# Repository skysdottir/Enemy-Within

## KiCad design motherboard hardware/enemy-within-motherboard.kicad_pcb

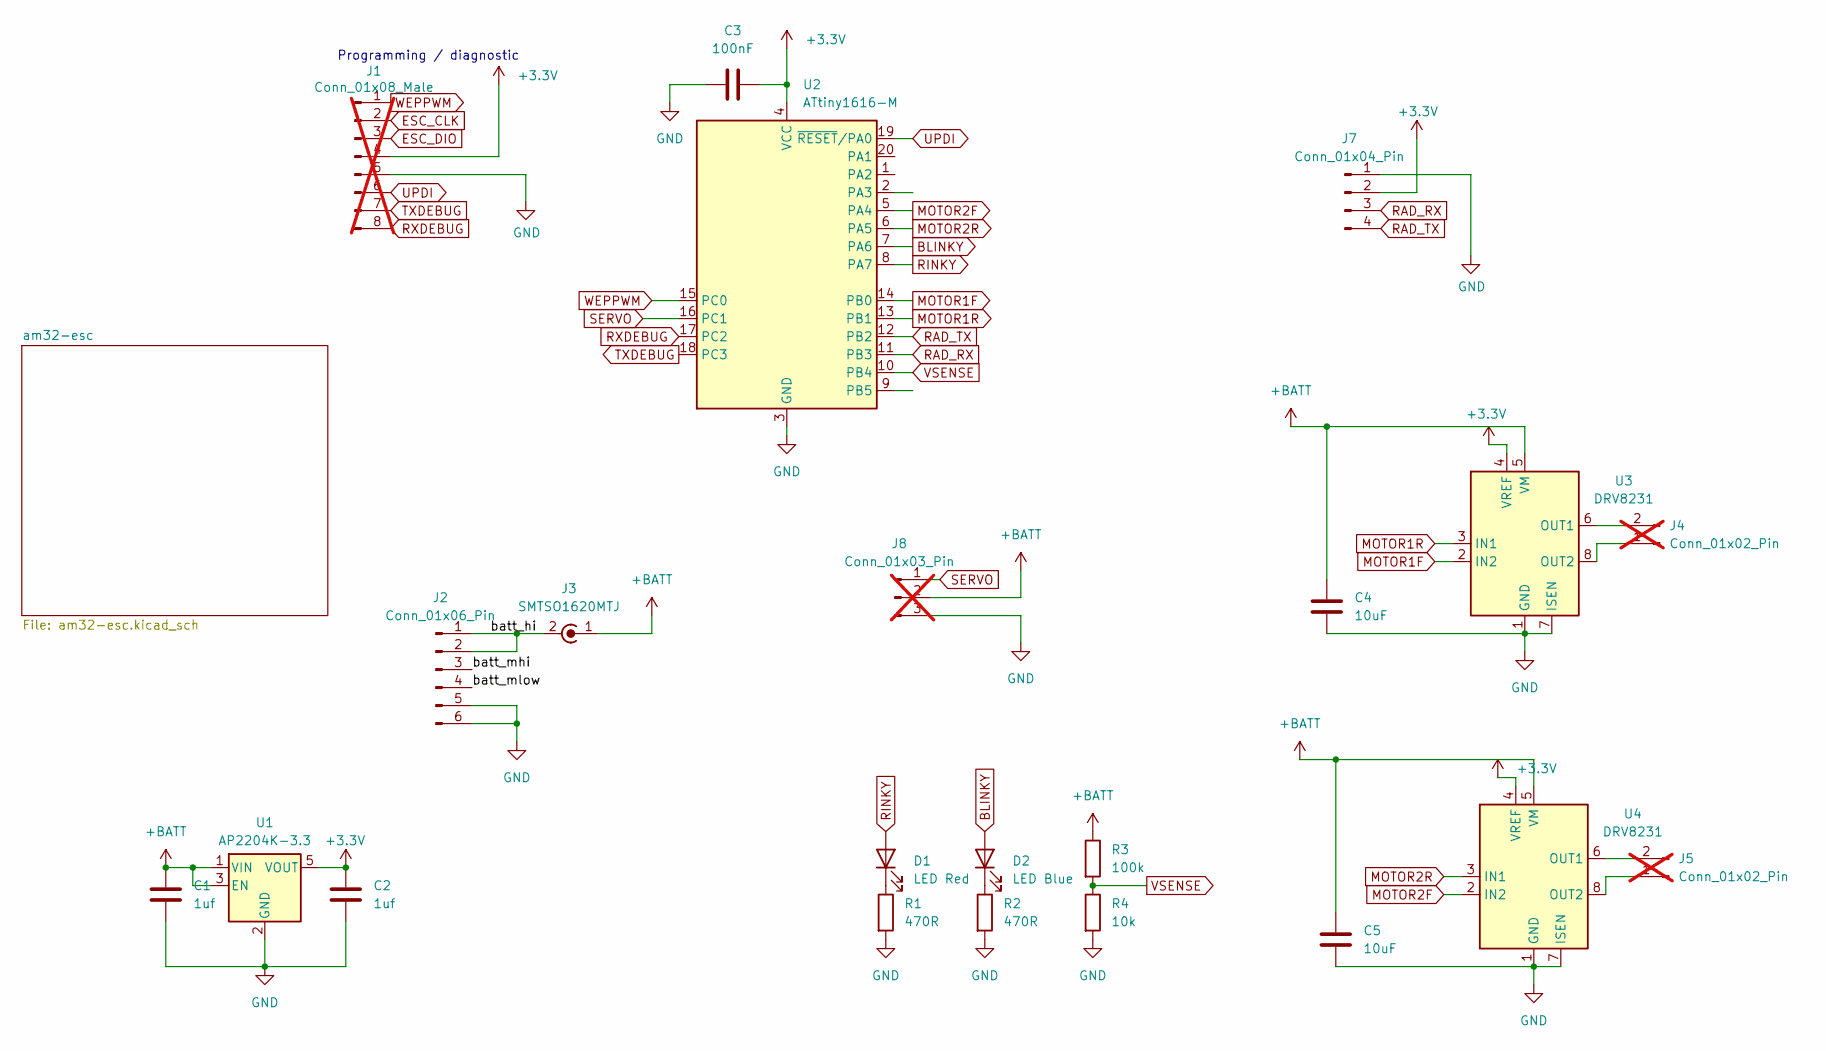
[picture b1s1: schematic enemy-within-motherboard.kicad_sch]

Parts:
C1, C2: 1uf; C_0402_1005Metric_Pad0.74x0.62mm_HandSolder
C3: 100nF; C_0402_1005Metric_Pad0.74x0.62mm_HandSolder
C4, C5: 10uF; C_0402_1005Metric_Pad0.74x0.62mm_HandSolder
D1: LED Red; LED_0603_1608Metric
D2: LED Blue; LED_0603_1608Metric
J1: Conn_01x08_Male; SOIC_clipProgSmall; not fitted
J2: Conn_01x06_Pin; JST_XH_B6B-XH-A_1x06_P2.50mm_Vertical
J3: SMTSO1620MTJ; MountingHole_2.2mm_M2_Pad_TopBottom
J4, J5: Conn_01x02_Pin; PinHeader_1x02_P2.54mm_Vertical; not fitted
J7: Conn_01x04_Pin; PinHeader_1x04_P2.54mm_Vertical
J8: Conn_01x03_Pin; PinHeader_1x03_P2.54mm_Vertical; not fitted
R1, R2: 470R; R_0402_1005Metric_Pad0.72x0.64mm_HandSolder
R3: 100k; R_0402_1005Metric_Pad0.72x0.64mm_HandSolder
R4: 10k; R_0402_1005Metric_Pad0.72x0.64mm_HandSolder
U1: AP2204K-3.3; TSOT-23-5
U2: ATtiny1616-M; VQFN-20-1EP_3x3mm_P0.4mm_EP1.7x1.7mm
U3, U4: DRV8231; WSON-8-1EP_2x2mm_P0.5mm_EP0.9x1.6mm

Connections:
+3.3V: C2.1, C3.2, J1.4, J7.2, U1.5 (VOUT), U2.4 (VCC), U3.4 (VREF), U4.4 (VREF); also elsewhere on the board
+BATT: C1.1, C4.1, C5.1, J3.1 (In), J8.2, R3.1, U1.1 (VIN), U1.3 (EN), U3.5 (VM), U4.5 (VM); also elsewhere on the board
/batt_hi: J2.1, J2.2, J3.2 (Ext)
/batt_mhi: J2.3
/batt_mlow: J2.4
BLINKY: D2.2 (A), U2.7 (PA6)
ESC_CLK: J1.2; also elsewhere on the board
ESC_DIO: J1.3; also elsewhere on the board
GND: C1.2, C2.2, C3.1, C4.2, C5.2, J1.5, J2.5, J2.6, J7.1, J8.3, R1.2, R2.2, R4.2, U1.2 (GND), U2.3 (GND), U2.21 (GND), U3.1 (GND), U3.7 (ISEN), U3.9 (GND), U4.1 (GND), U4.7 (ISEN), U4.9 (GND); also elsewhere on the board
MOTOR1F: U2.14 (PB0), U3.2 (IN2)
MOTOR1R: U2.13 (PB1), U3.3 (IN1)
MOTOR2F: U2.5 (PA4), U4.2 (IN2)
MOTOR2R: U2.6 (PA5), U4.3 (IN1)
unnamed: D1.1 (K), R1.1
unnamed: D2.1 (K), R2.1
unnamed: J4.1, U3.8 (OUT2)
unnamed: J4.2, U3.6 (OUT1)
unnamed: J5.1, U4.8 (OUT2)
unnamed: J5.2, U4.6 (OUT1)
RAD_RX: J7.3, U2.11 (PB3)
RAD_TX: J7.4, U2.12 (PB2)
RINKY: D1.2 (A), U2.8 (PA7)
RXDEBUG: J1.8, U2.17 (PC2)
SERVO: J8.1, U2.16 (PC1)
TXDEBUG: J1.7, U2.18 (PC3)
UPDI: J1.6, U2.19 (~RESET/PA0)
VSENSE: R3.2, R4.1, U2.10 (PB4); also elsewhere on the board
WEPPWM: J1.1, U2.15 (PC0); also elsewhere on the board

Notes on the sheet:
Programming / diagnostic

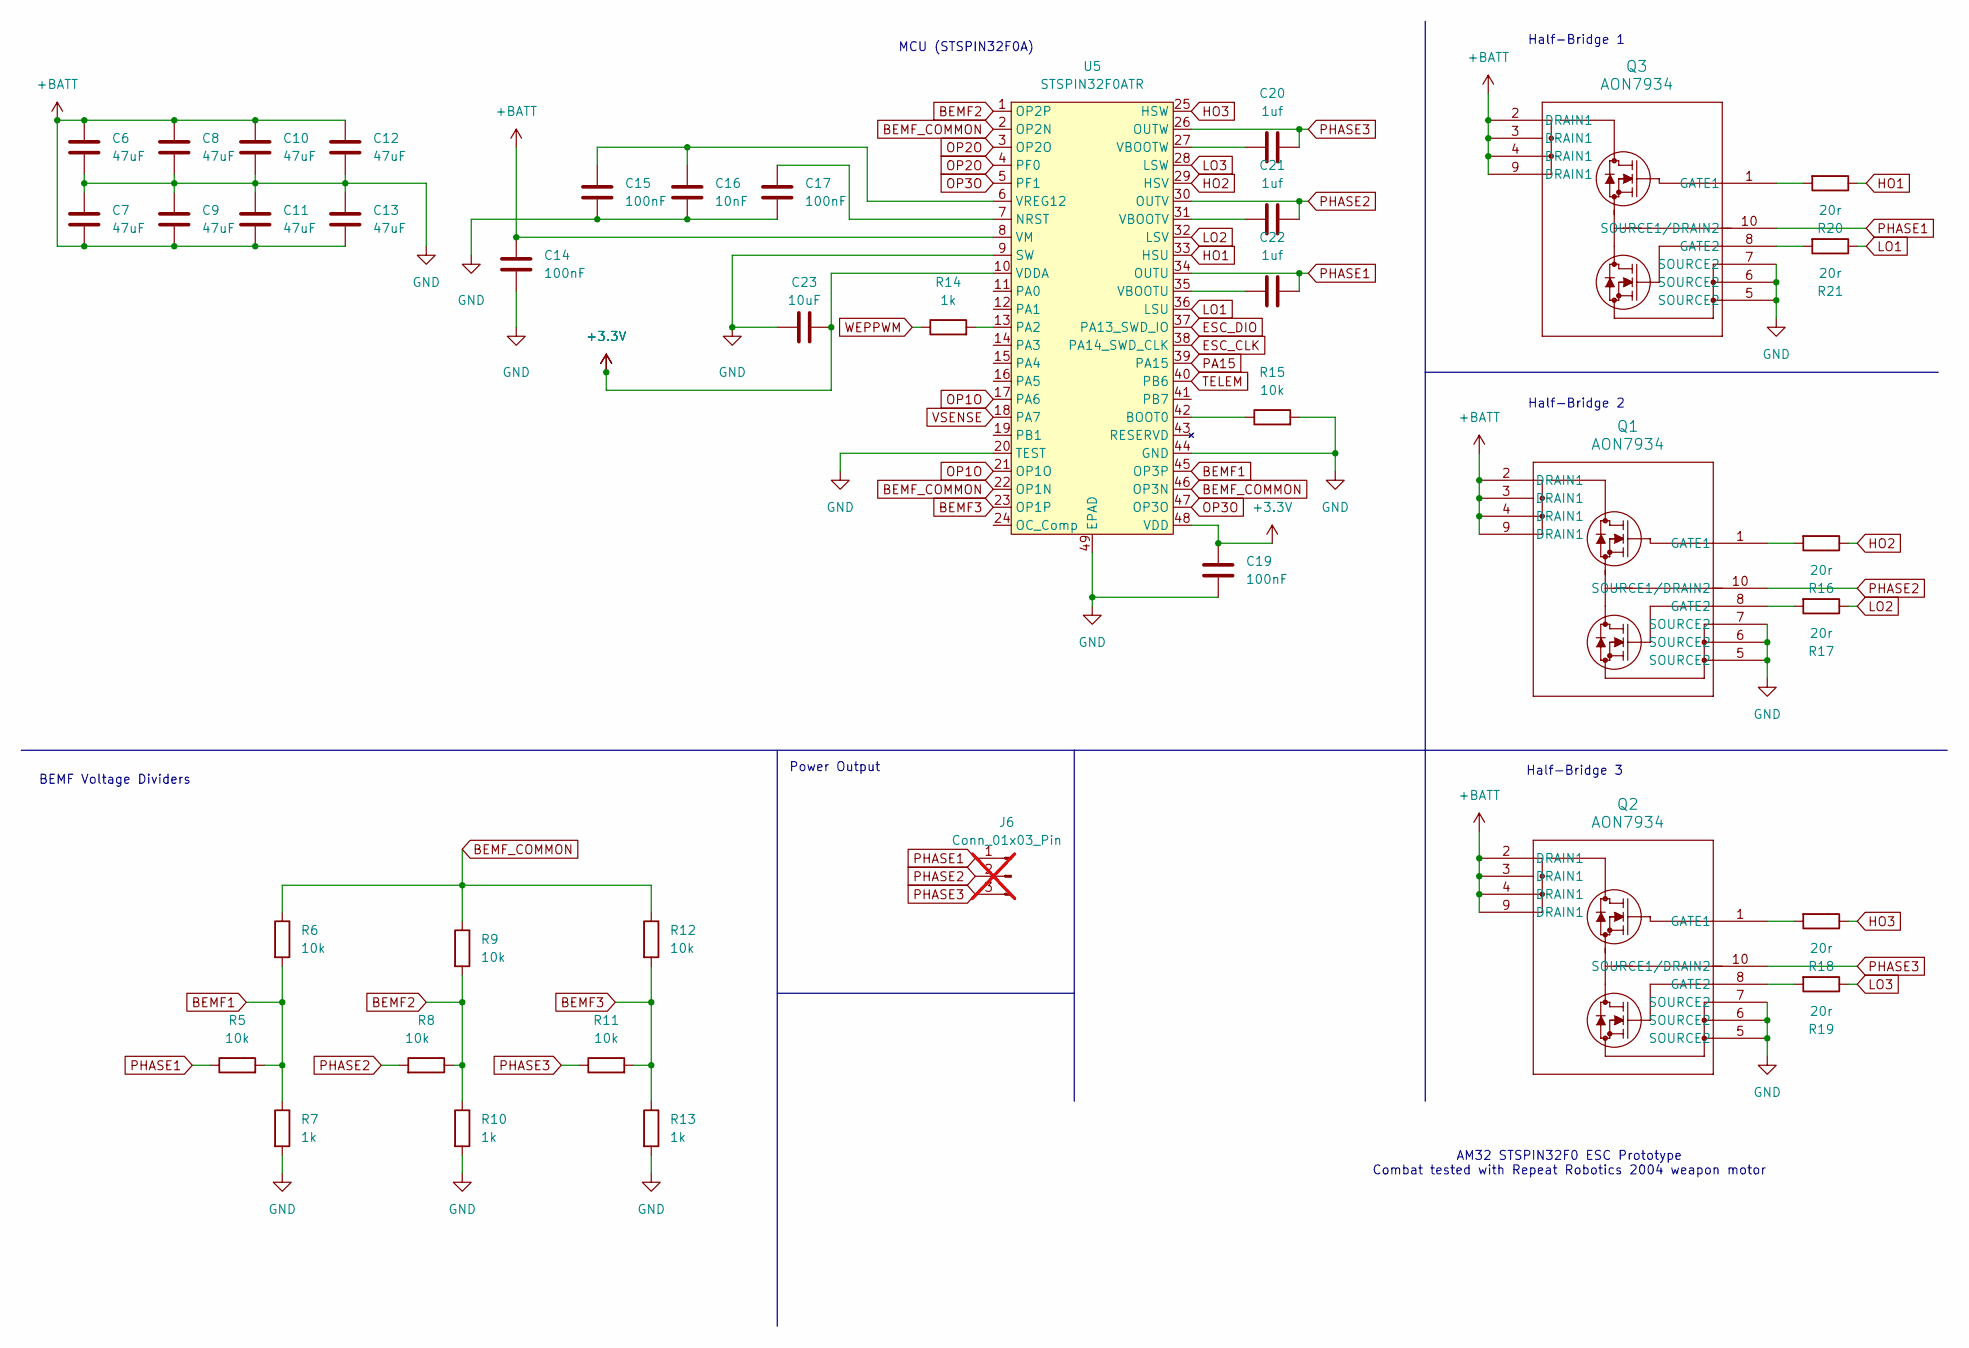
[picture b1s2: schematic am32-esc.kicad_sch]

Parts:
C6, C7, C8, C9, C10, C11, C12, C13: 47uF; C_0603_1608Metric
C14, C15, C17, C19: 100nF; C_0402_1005Metric_Pad0.74x0.62mm_HandSolder
C16: 10nF; C_0402_1005Metric_Pad0.74x0.62mm_HandSolder
C20, C21, C22: 1uf; C_0402_1005Metric_Pad0.74x0.62mm_HandSolder
C23: 10uF; C_0402_1005Metric_Pad0.74x0.62mm_HandSolder
J6: Conn_01x03_Pin; PinHeader_1x03_P2.54mm_Vertical; not fitted
Q1, Q2, Q3: AON7934; DFN3x3A_8L_EP2_S_AOS
R5, R6, R8, R9, R11, R12, R15: 10k; R_0402_1005Metric_Pad0.72x0.64mm_HandSolder
R7, R10, R13, R14: 1k; R_0402_1005Metric_Pad0.72x0.64mm_HandSolder
R16, R17, R18, R19, R20, R21: 20r; R_0402_1005Metric_Pad0.72x0.64mm_HandSolder
U5: STSPIN32F0ATR; QFN-48-1EP_7x7mm_P0.5mm_EP3.5x3.5mm

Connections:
+3.3V: C19.1, C23.1, U5.10 (VDDA), U5.48 (VDD); also elsewhere on the board
+BATT: C6.1, C7.2, C8.1, C9.2, C10.1, C11.2, C12.1, C13.2, C14.1, Q1.2 (DRAIN1), Q1.3 (DRAIN1), Q1.4 (DRAIN1), Q1.9 (DRAIN1), Q2.2 (DRAIN1), Q2.3 (DRAIN1), Q2.4 (DRAIN1), Q2.9 (DRAIN1), Q3.2 (DRAIN1), Q3.3 (DRAIN1), Q3.4 (DRAIN1), Q3.9 (DRAIN1), U5.8 (VM); also elsewhere on the board
BEMF1: R5.2, R6.2, R7.1, U5.45 (OP3P)
BEMF2: R8.1, R9.2, R10.1, U5.1 (OP2P)
BEMF3: R11.2, R12.2, R13.1, U5.23 (OP1P)
BEMF_COMMON: R6.1, R9.1, R12.1, U5.2 (OP2N), U5.22 (OP1N), U5.46 (OP3N)
ESC_CLK: U5.38 (PA14_SWD_CLK); also elsewhere on the board
ESC_DIO: U5.37 (PA13_SWD_IO); also elsewhere on the board
GND: C6.2, C7.1, C8.2, C9.1, C10.2, C11.1, C12.2, C13.1, C14.2, C15.2, C16.2, C17.2, C19.2, C23.2, Q1.5 (SOURCE2), Q1.6 (SOURCE2), Q1.7 (SOURCE2), Q2.5 (SOURCE2), Q2.6 (SOURCE2), Q2.7 (SOURCE2), Q3.5 (SOURCE2), Q3.6 (SOURCE2), Q3.7 (SOURCE2), R7.2, R10.2, R13.2, R15.2, U5.9 (SW), U5.20 (TEST), U5.44 (GND), U5.49 (EPAD); also elsewhere on the board
HO1: R20.1, U5.33 (HSU)
HO2: R16.1, U5.29 (HSV)
HO3: R18.1, U5.25 (HSW)
LO1: R21.1, U5.36 (LSU)
LO2: R17.1, U5.32 (LSV)
LO3: R19.1, U5.28 (LSW)
unnamed: Q1.1 (GATE1), R16.2
unnamed: Q1.8 (GATE2), R17.2
unnamed: Q2.1 (GATE1), R18.2
unnamed: Q2.8 (GATE2), R19.2
unnamed: Q3.1 (GATE1), R20.2
unnamed: Q3.8 (GATE2), R21.2
unnamed: R15.1, U5.42 (BOOT0)
unnamed: C17.1, U5.7 (NRST)
unnamed: R14.2, U5.13 (PA2)
unnamed: C22.1, U5.35 (VBOOTU)
unnamed: C21.1, U5.31 (VBOOTV)
unnamed: C20.1, U5.27 (VBOOTW)
unnamed: C15.1, C16.1, U5.6 (VREG12)
OP1O: U5.17 (PA6), U5.21 (OP1O)
OP2O: U5.3 (OP2O), U5.4 (PF0)
OP3O: U5.5 (PF1), U5.47 (OP3O)
PA15: U5.39 (PA15)
PHASE1: C22.2, J6.1, Q3.10 (SOURCE1/DRAIN2), R5.1, U5.34 (OUTU)
PHASE2: C21.2, J6.2, Q1.10 (SOURCE1/DRAIN2), R8.2, U5.30 (OUTV)
PHASE3: C20.2, J6.3, Q2.10 (SOURCE1/DRAIN2), R11.1, U5.26 (OUTW)
TELEM: U5.40 (PB6)
VSENSE: U5.18 (PA7); also elsewhere on the board
WEPPWM: R14.1; also elsewhere on the board

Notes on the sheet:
Half-Bridge 3
Half-Bridge 2
AM32 STSPIN32F0 ESC Prototype Combat tested with Repeat Robotics 2004 weapon motor
Half-Bridge 1
Power Output
BEMF Voltage Dividers
MCU (STSPIN32F0A)

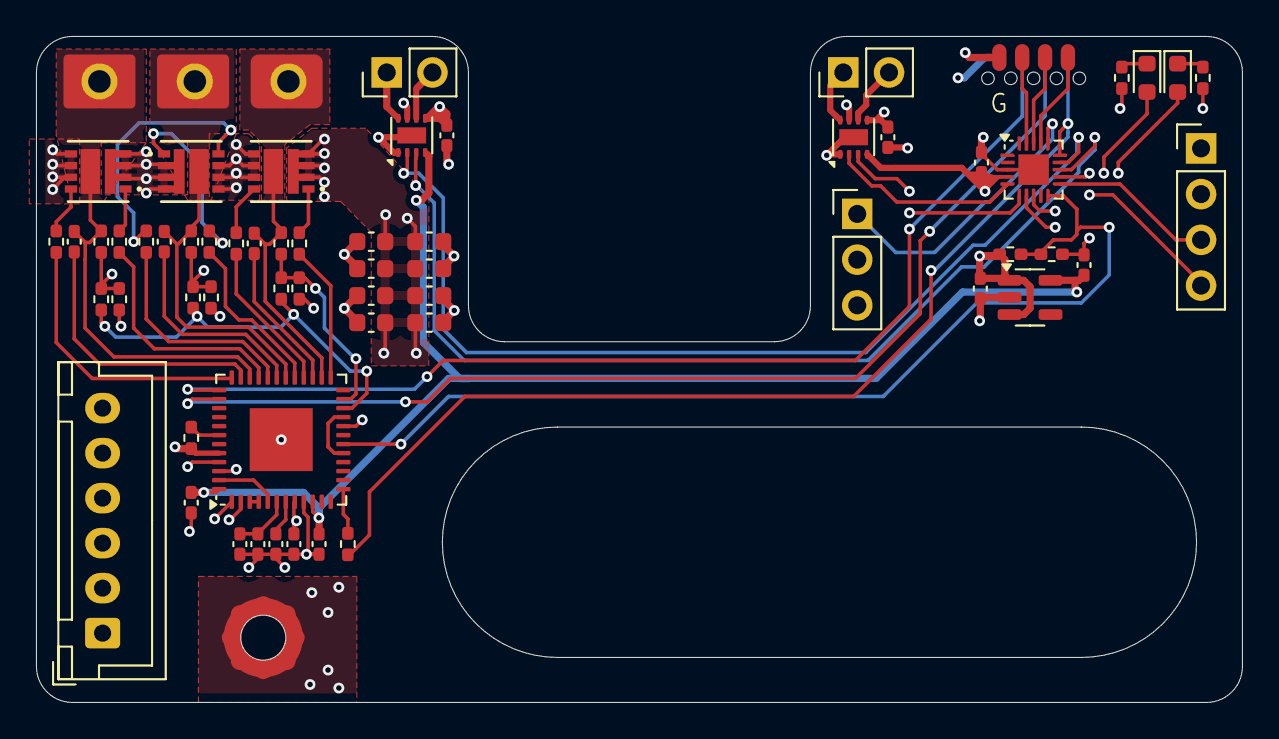
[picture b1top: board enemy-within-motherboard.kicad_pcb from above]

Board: 4 copper layers, 67.0 x 37.0 mm, 61 parts (1 on the bottom side), 55 nets.

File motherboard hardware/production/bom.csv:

Designator,Footprint,Quantity,Value,LCSC Part #
"C1, C2, C20, C21, C22",0402,5,1uf,
"C10, C11, C12, C13, C6, C7, C8, C9",0603,8,47uF,
"C14, C15, C17, C19, C3",0402,5,100nF,
C16,0402,1,10nF,
"C23, C4, C5",0402,3,10uF,
D1,0603,1,LED Red,
D2,0603,1,LED Blue,
J2,JST_XH_B6B-XH-A_1x06_P2.50mm_Vertical,1,Conn_01x06_Pin,
J3,MountingHole_2.2mm_M2_Pad_TopBottom,1,SMTSO1620MTJ,
"J4, J5",PinHeader_1x02_P2.54mm_Vertical,2,Conn_01x02_Pin,
"J6, J8",PinHeader_1x03_P2.54mm_Vertical,2,Conn_01x03_Pin,
J7,PinHeader_1x04_P2.54mm_Vertical,1,Conn_01x04_Pin,
"Q1, Q2, Q3",DFN3x3A_8L_EP2_S_AOS,3,AON7934,
"R1, R2",0402,2,470R,
"R10, R13, R14, R7",0402,4,1k,
"R11, R12, R15, R4, R5, R6, R8, R9",0402,8,10k,
"R16, R17, R18, R19, R20, R21",0402,6,20r,
R3,0402,1,100k,
U1,TSOT-23-5,1,AP2204K-3.3,
U2,VQFN-20-1EP_3x3mm_P0.4mm_EP1.7x1.7mm,1,ATtiny1616-M,
"U3, U4",WSON-8-1EP_2x2mm_P0.5mm_EP0.9x1.6mm,2,DRV8231,
U5,QFN-48-1EP_7x7mm_P0.5mm_EP3.5x3.5mm,1,STSPIN32F0ATR,

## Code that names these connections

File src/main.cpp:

#include <Arduino.h>
#include <sbus.h> // Bolder Flight Systems SBUS
#include <Servo_megaTinyCore.h>
#include <SoftwareSerial.h>
#include <Adafruit_NeoPixel.h>

#define RFWD PIN_PA5
#define RREV PIN_PA4

#define LFWD PIN_PB0
#define LREV PIN_PB1

#define BLUE PIN_PA6
#define RED PIN_PA7

#define TXDEBUG PIN_PC3
#define RXDEBUG PIN_PC2

#define WEP_PIN PIN_PC0
#define SERVO_PIN PIN_PC1

#define CONTROL_MOTION_TIMEOUT_MS 3000

bfs::SbusRx sbus_rx(&Serial);
bfs::SbusData data;

Adafruit_NeoPixel pixels(17, SERVO_PIN, NEO_GRB+NEO_KHZ800);

#ifdef DEBUG_MODE
SoftwareSerial dbgSerial(RXDEBUG, TXDEBUG);
#endif

unsigned long control_checksum;
unsigned long last_changed_at;
boolean startup = true;

Servo motor;

void setup() {
  #ifdef DEBUG_MODE
  dbgSerial.begin(9600);

  dbgSerial.println("setup begin");
  #endif

  motor.attach(WEP_PIN);
  motor.writeMicroseconds(1500);

  pinMode(RFWD, OUTPUT);
  pinMode(RREV, OUTPUT);

  pinMode(LFWD, OUTPUT);
  pinMode(LREV, OUTPUT);

  pinMode(RED, OUTPUT);
  pinMode(BLUE, OUTPUT);
  digitalWrite(RED, HIGH);

  analogWrite(LREV, 0);
  analogWrite(RREV, 0);
  analogWrite(LFWD, 0);
  analogWrite(RFWD, 0);

  sbus_rx.Begin();

  pixels.begin();

  #ifdef DEBUG_MODE
  dbgSerial.println("setup done");
  #endif
}

bool rc_poll() {
  if (sbus_rx.Read()) {
    data = sbus_rx.data();
    return true;
  }

  return false;
}

int get_ch(int ch) {
  // 11-bit channel, range from 172-1811
  int pulse_len = data.ch[ch];

  // reduce to 0..1639
  pulse_len -= 172;

  // reduce to 0..512
  float norm = pulse_len * (512.0/1639.0);

  // and normalize to -255-255
  pulse_len = norm - 255;

  return pulse_len;
}

int lim_8(int in) {
  if (in > 255) {
    return 255;
  }

  if (in < -255) {
    return -255;
  }

  // center deadzone
  if(in < 10 && in > -10) {
    return 0;
  }

  return in;
}

unsigned long compute_checksum() {
  return data.ch[0]*64 + data.ch[1]*16 + data.ch[2]*4 + data.ch[3];
}

bool rc_signal_is_healthy() {
  unsigned long new_checksum = compute_checksum();
  unsigned long now = millis();
  bool pass = false;
  if (new_checksum != control_checksum) {
    last_changed_at = now;
    control_checksum = new_checksum;
    pass = true;
    startup = false;
  } else if(!startup) {
    pass = ((now - last_changed_at) < CONTROL_MOTION_TIMEOUT_MS);
  }
  return pass;
}

void loop() {
  rc_poll();

  // default to: Neutral drive controls, minimum (off) weapon throttle
  int forback = 0;
  int leftright = 0;
  int throttle = 0;

  if(rc_signal_is_healthy()) {
    forback = get_ch(1);
    leftright = get_ch(0);
    throttle = get_ch(2);
    digitalWrite(BLUE, HIGH);
  }
  else {
    digitalWrite(BLUE, LOW);
  }

  // mixing time!
  int ldrv = lim_8(forback + leftright);
  int rdrv = lim_8(forback - leftright);

  if (ldrv > 0) {
    analogWrite(LFWD, ldrv);
    analogWrite(LREV, 0);
  } else {
    analogWrite(LFWD, 0);
    analogWrite(LREV, ldrv*-1);
  }

  if (rdrv > 0) {
    analogWrite(RFWD, rdrv);
    analogWrite(RREV, 0);
  } else {
    analogWrite(RFWD, 0);
    analogWrite(RREV, rdrv*-1);
  }

  int wthrtl = map(throttle, -255, 255, 1000, 2000);
  motor.writeMicroseconds(wthrtl);

  #ifdef DEBUG_MODE
  if(millis() % 1024 < 20) {
    dbgSerial.print("ldrv: ");
    dbgSerial.print(ldrv);
    dbgSerial.print(" rdrv: ");
    dbgSerial.print(rdrv);
    dbgSerial.print(" Throttle setting ms: ");
    dbgSerial.println(wthrtl);
  }
  #endif

  long now = millis();
  int shortnow = (now * 64)%65536;

  pixels.clear();
  for(int i = 0; i < 17; i++) {
    pixels.setPixelColor(i, pixels.ColorHSV(shortnow + i*6*256));
  }
  pixels.show();

  delay(20);
}

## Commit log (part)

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2026-01-05 New repo
2026-01-05 Rebuilt Enemy Within code
2026-01-28 Added PCB design
